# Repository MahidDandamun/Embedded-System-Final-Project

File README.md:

# Automated Pet Feeder System

An open-source, IoT-enabled automated pet feeder built with ESP32. Schedule feedings, monitor your pet's eating habits in real-time, and control everything from your phone.

<!--  -->

## Features

- **Scheduled Auto-Feeding** — 4 configurable daily feeding times
- **Manual Feed** — Physical button or remote trigger from mobile app
- **Food Level Monitoring** — Ultrasonic sensor detects container level (FULL / HALF / EMPTY)
- **Bowl Weight Tracking** — HX711 load cell measures food in the bowl
- **Pet Detection** — PIR motion sensor detects animal presence
- **Mobile App Control** — React Native app connects via Bluetooth (BLE)
- **Cloud Telemetry** — Azure IoT Hub (MQTT) + REST API for data logging
- **Web Flasher** — Flash firmware from your browser via USB — no IDE needed
- **Status Display** — 16x2 LCD + RGB LED + buzzer feedback
- **Safety Limits** — Daily max (200g), minimum interval (5 min), bowl-full detection

## Repository Structure

```
├── firmware/               # ESP32 firmware (PlatformIO / C++)
│   ├── include/            #   Header files + config
│   ├── src/                #   Source files
│   ├── test/               #   Calibration test
│   └── platformio.ini
├── PCB/                    # KiCad PCB design for breakout board
├── 3D-MODEL/               # Fusion 360 housing + component mounts
├── docs/                   # Specs for mobile app & web flasher
│   ├── MOBILE_APP_SPEC.md  #   React Native mobile app spec
│   └── WEB_FLASHER_SPEC.md #   Next.js web flasher spec
├── .agents/                # AI agent rules, workflows, context
└── README.md               # You are here
```

### Companion Repositories (Separate)

| Repo | Tech Stack | Purpose |
|------|-----------|---------|
| `petfeeder-mobile` | React Native (Expo) + TypeScript | Mobile app — BLE control, dashboard, history |
| `petfeeder-web` | Next.js + Web Serial API | Browser-based firmware flasher & calibration |

## Hardware Requirements

| Component | Model | Qty |
|-----------|-------|-----|
| Microcontroller | ESP32 DevKit C | 1 |
| Ultrasonic Sensor | HC-SR04 | 1 |
| Load Cell + Amplifier | 5kg load cell + HX711 | 1 |
| PIR Motion Sensor | Generic | 1 |
| Servo Motor | SG90 or MG90S | 1 |
| LCD Display | 16x2 I2C (address 0x27) | 1 |
| RTC Module | DS1302 | 1 |
| RGB LED | Common cathode | 1 |
| Active Buzzer | 5V | 1 |
| Push Buttons | IP65 12mm momentary (x2) | 2 |
| Power Supply | 5V 2A, 5.5x2.1mm barrel jack | 1 |
| Rocker Switch | SPST | 1 |
| Custom PCB | See `PCB/` directory | 1 |
| 3D-Printed Housing | See `3D-MODEL/` directory | 1 |

## Quick Start

### 1. Clone

```bash
git clone https://github.com/MahidDandamun/Embedded-System-Final-Project.git
cd Embedded-System-Final-Project
```

### 2. Configure Secrets

```bash
cd firmware
cp include/secrets.h.template include/secrets.h
```

Edit `firmware/include/secrets.h` with your credentials:

```c
#define ENV_WIFI_SSID       "YourWiFi"
#define ENV_WIFI_PASSWORD   "YourPassword"
#define ENV_MQTT_SERVER     "your-hub.azure-devices.net"
#define ENV_MQTT_PORT       8883
#define ENV_DEVICE_ID       "petfeeder"
#define ENV_SAS_TOKEN       "SharedAccessSignature sr=..."
#define ENV_MQTT_USERNAME   "your-hub.azure-devices.net/petfeeder/?api-version=2021-04-12"
#define ENV_DATABASE_ENDPOINT "https://your-api.azurewebsites.net/api/devices/status"
```

> **Never commit `secrets.h`** — it's in `.gitignore`.

### 3. Build & Flash

```bash
# Install PlatformIO CLI
pip install platformio

# Build
pio run

# Upload to ESP32
pio run -t upload

# Monitor serial output
pio device monitor
```

### 4. Calibrate Load Cell

```bash
# Upload calibration firmware
pio test -e esp32dev -f test_calibration
```

Follow the serial prompts to find your `CALIBRATION_FACTOR`, then update it in `firmware/include/config.h`.

### 5. Assemble Hardware

1. Print the housing from `3D-MODEL/` (see [3D-MODEL/README.md](3D-MODEL/README.md))
2. Solder or order the PCB from `PCB/` (see [PCB/README.md](PCB/README.md))
3. Wire everything per the [pin mapping](firmware/README.md#pin-mapping-pcb-v2)
4. Power on and verify via serial monitor

## Architecture

```
┌─────────────┐     BLE      ┌─────────────┐
│  Mobile App │◄────────────►│    ESP32     │
│ (React Native)             │  Firmware    │
└─────────────┘              │             │
                             │  Sensors:    │
┌─────────────┐    MQTT      │  - Ultrasonic│
│  Azure IoT  │◄────────────►│  - Load Cell │
│    Hub      │              │  - PIR       │
└──────┬──────┘              │  - RTC       │
       │                     │             │
       │ REST                │  Actuators:  │
       ▼                     │  - Servo     │
┌─────────────┐              │  - LCD       │
│  Backend DB │              │  - RGB LED   │
│  (REST API) │              │  - Buzzer    │
└─────────────┘              └──────┬───────┘
                                    │ USB
┌─────────────┐    Web Serial      │
│  Web Flasher│◄───────────────────┘
│  (Next.js)  │
└─────────────┘
```

## Mobile App

The companion mobile app (separate repo) provides:

- **Dashboard** — Real-time sensor data, feeding status, pet detection
- **Feeding History** — Charts and timeline of all feeding events
- **Schedule Control** — Edit feeding times and portion sizes
- **BLE Connection** — Direct Bluetooth communication with the feeder
- **Push Notifications** — Low food alerts, missed feeding warnings

**Tech Stack:** React Native (Expo) + TypeScript + Zustand + react-native-ble-plx

See full spec: [docs/MOBILE_APP_SPEC.md](docs/MOBILE_APP_SPEC.md)

## Web Flasher

A browser-based tool to flash firmware and calibrate sensors — no IDE installation required:

1. Connect ESP32 via USB-C
2. Enter WiFi/cloud credentials in the web form
3. Click "Flash" — firmware uploads directly from Chrome
4. Run guided sensor calibration

**Tech Stack:** Next.js + TypeScript + Web Serial API + esptool-js

See full spec: [docs/WEB_FLASHER_SPEC.md](docs/WEB_FLASHER_SPEC.md)

## Pin Mapping

| Function | GPIO | Notes |
|----------|------|-------|
| Power Relay | 27 | System power control |
| Button 1 (Refill) | 15 | INPUT_PULLUP |
| Button 2 (Feed) | 0 | INPUT_PULLUP |
| Ultrasonic Trig | 32 | |
| Ultrasonic Echo | 33 | |
| PIR Sensor | 25 | |
| HX711 DOUT | 5 | |
| HX711 SCK | 23 | |
| RGB Red | 13 | |
| RGB Green | 12 | |
| RGB Blue | 14 | |
| Buzzer | 26 | Active buzzer |
| Servo | 4 | SG90/MG90S |
| RTC IO | 16 | DS1302 |
| RTC SCLK | 17 | DS1302 |
| RTC CE | 2 | DS1302 |

## Security Notes

- All credentials are stored in `secrets.h` which is **never committed** to git
- A `secrets.h.template` is provided as reference
- Azure SAS tokens should be rotated regularly
- For production: replace `setInsecure()` with proper TLS certificate pinning
- If you ever accidentally commit secrets: **rotate ALL credentials immediately**

### Regarding Credentials in Git History

The credentials found in older commits have been **revoked and are no longer valid**. The WiFi password, Azure SAS tokens, and API endpoints from the git history are all invalidated. Always generate your own fresh credentials.

## Contributing

1. Fork the repository
2. Create a feature branch (`git checkout -b feat/amazing-feature`)
3. Use conventional commits (`feat:`, `fix:`, `docs:`, `refactor:`)
4. Ensure no secrets are in your commits
5. Open a Pull Request

## License

This project is licensed under the [MIT License](LICENSE).

## Authors

- Irish Micole Cando
- Jelisha Bugnon
- Angela Corpuz
- Mahid Dandamun
- Miguel Alfonso Neri

---

> Built as a final project for Embedded Systems course. Designed to be open-source, educational, and production-ready.

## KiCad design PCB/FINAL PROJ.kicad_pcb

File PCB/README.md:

# PCB — Pet Feeder Breakout Board

KiCad PCB design for the ESP32 pet feeder breakout/carrier board.

## Files

| File | Description |
|------|-------------|
| `FINAL PROJ.kicad_sch` | Schematic |
| `FINAL PROJ.kicad_pcb` | PCB layout |
| `FINAL PROJ.kicad_pro` | KiCad project |
| `FINAL PROJ.step` | 3D model of PCB |
| `freerouting.dsn` | Auto-routing export |
| `config.h` | Pin mapping reference (mirrors firmware config) |

## Features

- ESP32 DevKit C socket
- Breakout headers for all sensors (HC-SR04, PIR, HX711, DS1302)
- Servo connector (5V + signal)
- I2C header for LCD
- RGB LED + buzzer outputs
- 5V barrel jack power input with rocker switch
- Dual push-button inputs

## Opening the Design

1. Install [KiCad](https://www.kicad.org/) (v7+ recommended)
2. Open `FINAL PROJ.kicad_pro`
3. Schematic → `FINAL PROJ.kicad_sch`
4. PCB Layout → `FINAL PROJ.kicad_pcb`

## Manufacturing

Export Gerbers from KiCad and upload to your preferred PCB fab (JLCPCB, PCBWay, OSH Park, etc.).

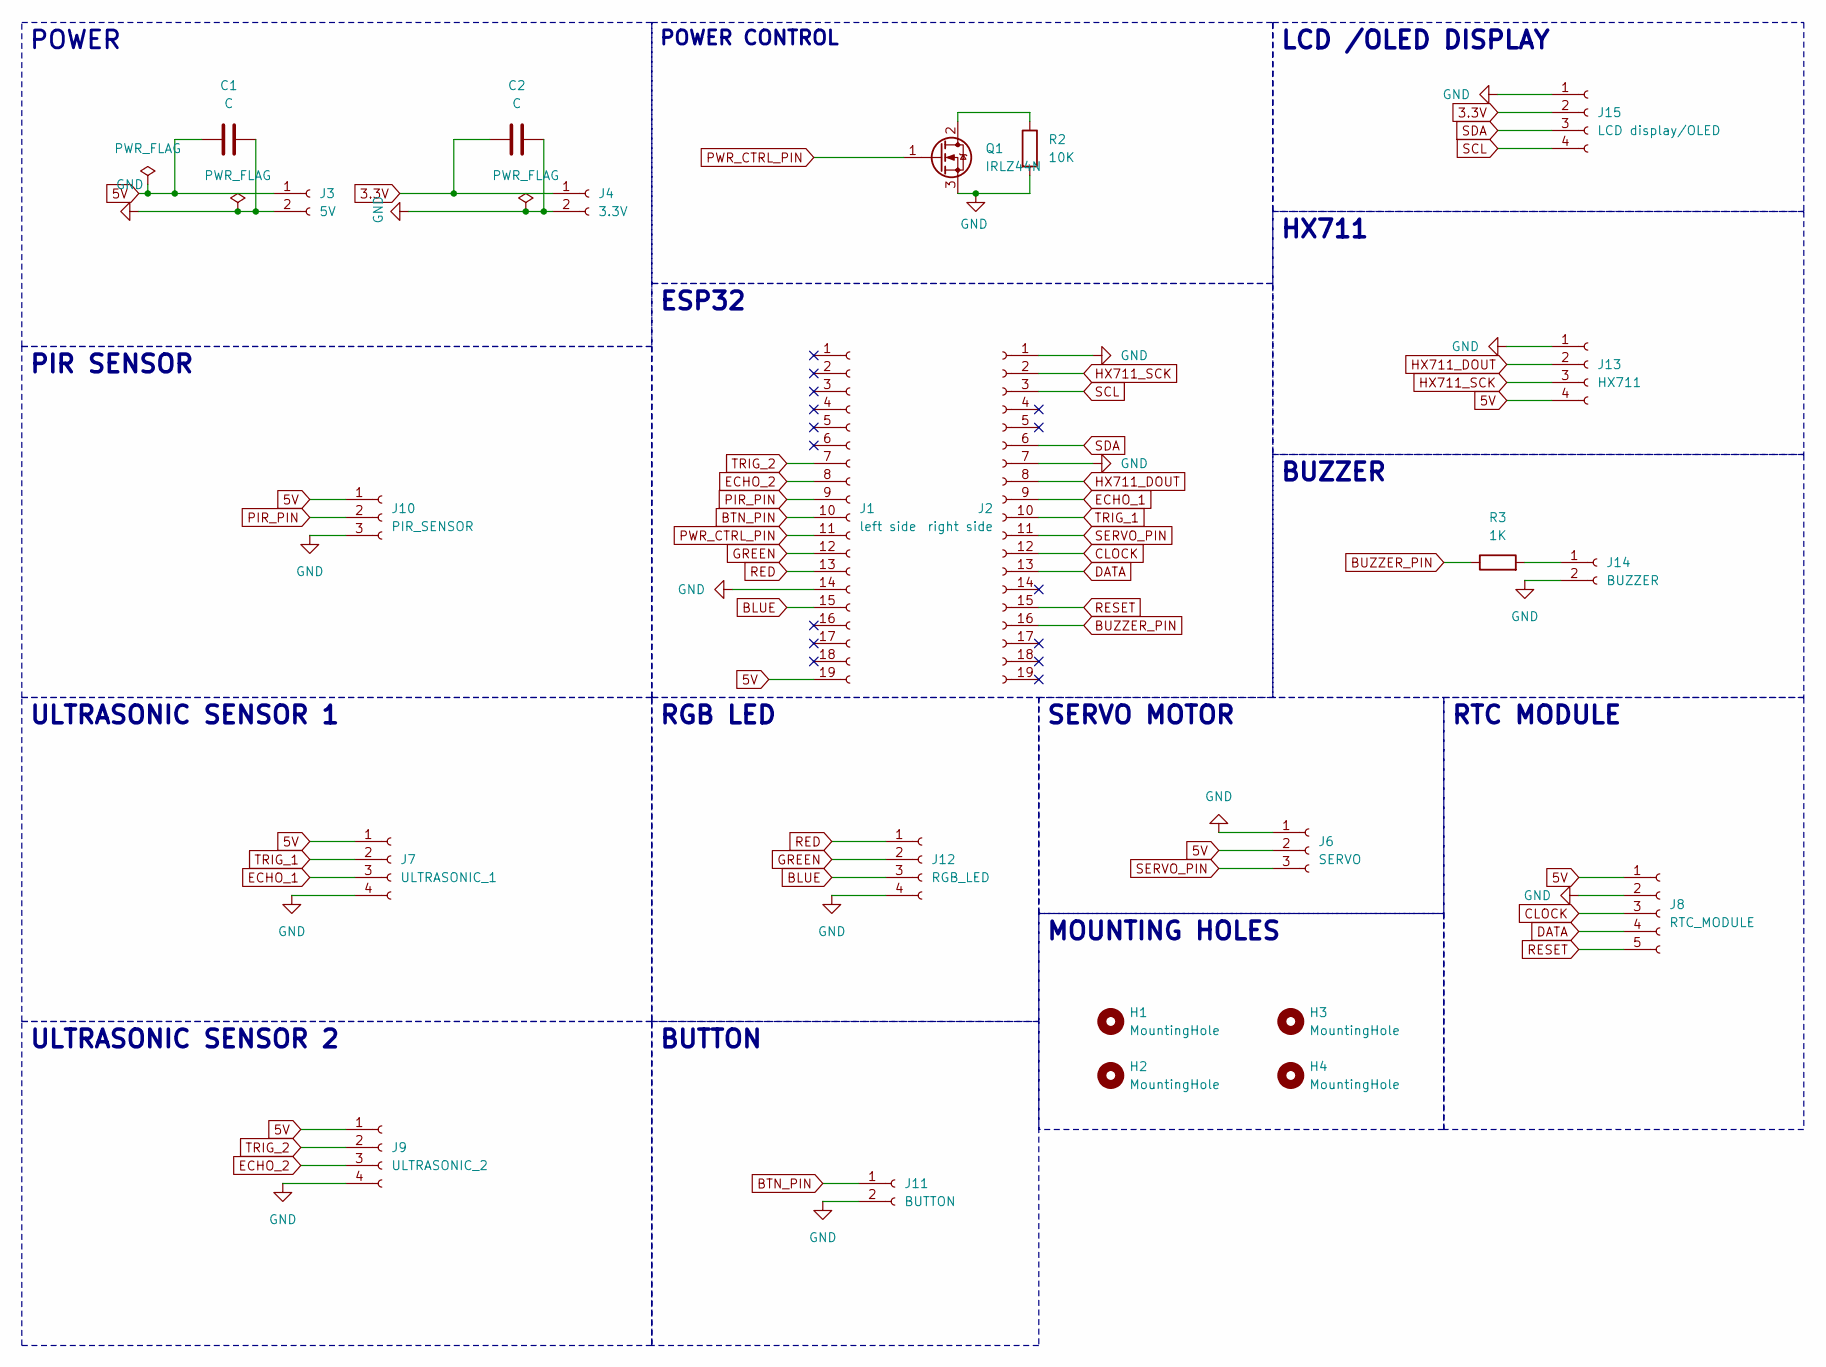
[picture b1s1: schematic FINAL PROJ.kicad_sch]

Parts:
C1, C2: C; C_Disc_D4.3mm_W1.9mm_P5.00mm
H1, H2, H3, H4: MountingHole; MountingHole_3.2mm_M3
J1: left side; PinSocket_1x19_P2.54mm_Vertical
J2: right side; PinSocket_1x19_P2.54mm_Vertical
J3: 5V; JST_EH_B2B-EH-A_1x02_P2.50mm_Vertical
J4: 3.3V; JST_EH_B2B-EH-A_1x02_P2.50mm_Vertical
J6: SERVO; JST_EH_B3B-EH-A_1x03_P2.50mm_Vertical
J7: ULTRASONIC_1; JST_EH_B4B-EH-A_1x04_P2.50mm_Vertical
J8: RTC_MODULE; PinSocket_1x05_P2.54mm_Vertical
J9: ULTRASONIC_2; JST_EH_B4B-EH-A_1x04_P2.50mm_Vertical
J10: PIR_SENSOR; JST_EH_B3B-EH-A_1x03_P2.50mm_Vertical
J11: BUTTON; JST_EH_B2B-EH-A_1x02_P2.50mm_Vertical
J12: RGB_LED; JST_EH_B4B-EH-A_1x04_P2.50mm_Vertical
J13: HX711; PinSocket_1x04_P2.54mm_Vertical
J14: BUZZER; JST_EH_B2B-EH-A_1x02_P2.50mm_Vertical
J15: LCD display/OLED; JST_EH_B4B-EH-A_1x04_P2.50mm_Vertical
Q1: IRLZ44N; TO-220-3_Vertical
R2: 10K; R_Axial_DIN0309_L9.0mm_D3.2mm_P12.70mm_Horizontal
R3: 1K; R_Axial_DIN0309_L9.0mm_D3.2mm_P12.70mm_Horizontal

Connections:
3.3V: C2.1, J4.1, J15.2
5V: C1.1, J1.19, J3.1, J6.2, J7.1, J8.1, J9.1, J10.1, J13.4
BLUE: J1.15, J12.3
BTN_PIN: J1.10, J11.1
BUZZER_PIN: J2.16, R3.1
CLOCK: J2.12, J8.3
DATA: J2.13, J8.4
ECHO_1: J2.9, J7.3
ECHO_2: J1.8, J9.3
GREEN: J1.12, J12.2
HX711_DOUT: J2.8, J13.2
HX711_SCK: J2.2, J13.3
unnamed: J14.1, R3.2
unnamed: Q1.2 (D), R2.1
PIR_PIN: J1.9, J10.2
PWR_CTRL_PIN: J1.11, Q1.1 (G)
RED: J1.13, J12.1
RESET: J2.15, J8.5
SCL: J2.3, J15.4
SDA: J2.6, J15.3
SERVO_PIN: J2.11, J6.3
TRIG_1: J2.10, J7.2
TRIG_2: J1.7, J9.2

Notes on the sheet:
HX711
PIR SENSOR
RGB LED
BUTTON
MOUNTING HOLES
ESP32
ULTRASONIC SENSOR 1
ULTRASONIC SENSOR 2
BUZZER
POWER CONTROL
RTC MODULE
POWER
LCD /OLED DISPLAY
SERVO MOTOR

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
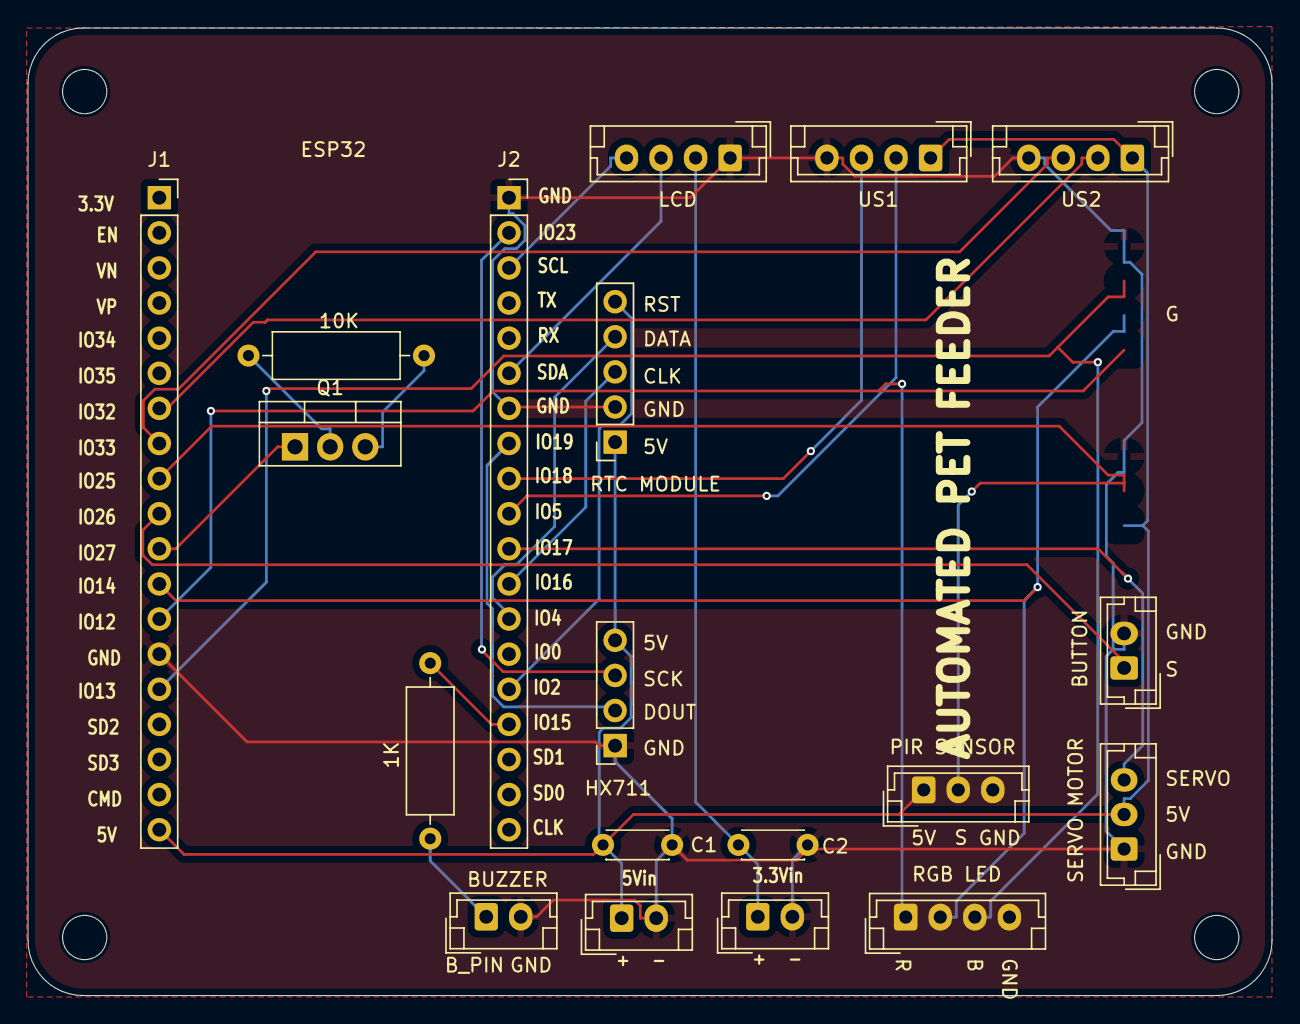
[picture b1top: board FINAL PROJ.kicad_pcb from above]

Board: 2 copper layers, 90.0 x 70.0 mm, 23 parts (1 on the bottom side), 25 nets.

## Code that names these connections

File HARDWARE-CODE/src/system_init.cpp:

#include "system_init.h"

void systemStart()
{
  initializeLCD();
  initializeRTC();
  initializePins();
  initializeWiFi();
  initializeSensors();
  feederSystem.initialized = true;

  lcd.clear();
  lcd.setCursor(0, 0);
  lcd.print("Pet Feeder Ready");
  lcd.setCursor(0, 1);
  lcd.print("HTTP Mode");
}

void initializeLCD()
{
  lcd.init();
  lcd.backlight();
  lcd.setCursor(0, 0);
  lcd.print("Initializing...");
}

void initializeRTC()
{
  if (rtc.begin())
  {
    feederSystem.rtcReady = true;
    if (rtc.lostPower())
      rtc.adjust(DateTime(F(__DATE__), F(__TIME__)));

    DateTime now = rtc.now();
    timeData.lastAutoFeedTime = now;
    timeData.nextScheduledFeed = getNextScheduledFeedTime(now);
    timeData.currentTimeString = formatTime(now);
    timeData.nextFeedTimeString = formatTime(timeData.nextScheduledFeed);

    lcd.setCursor(0, 1);
    lcd.print("RTC: OK");
  }
  else
  {
    feederSystem.rtcReady = false;
    feederSystem.autoFeedingEnabled = false;
    lcd.setCursor(0, 1);
    lcd.print("RTC: FAILED");
  }
  delay(1000);
}

void initializePins()
{
  pinMode(POWER_PIN, OUTPUT);
  digitalWrite(POWER_PIN, HIGH);
  feederSystem.powerOn = true;

  pinMode(BUTTON1_PIN, INPUT_PULLUP);
  pinMode(BUTTON2_PIN, INPUT_PULLUP);
  pinMode(ULTRASONIC_TRIG_PIN, OUTPUT);
  pinMode(ULTRASONIC_ECHO_PIN, INPUT);
  pinMode(PIR_PIN, INPUT);
  pinMode(HX711_DOUT_PIN, INPUT);
  pinMode(HX711_SCK_PIN, OUTPUT);
  pinMode(RED_PIN, OUTPUT);
  pinMode(GREEN_PIN, OUTPUT);
  pinMode(BLUE_PIN, OUTPUT);
  pinMode(BUZZER_PIN, OUTPUT);

  myServo.attach(SERVO_PIN);
  myServo.write(0);
}

void initializeWiFi()
{
  lcd.clear();
  lcd.setCursor(0, 0);
  lcd.print("Connecting WiFi");
  WiFi.begin(WIFI_SSID, WIFI_PASSWORD);

  int attempts = 0;
  while (WiFi.status() != WL_CONNECTED && attempts < WIFI_RETRY_ATTEMPTS)
  {
    delay(500);
    lcd.setCursor(attempts % LCD_COLUMNS, 1);
    lcd.print(".");
    attempts++;
  }

  lcd.clear();
  lcd.setCursor(0, 0);
  if (WiFi.status() == WL_CONNECTED)
  {
    lcd.print("WiFi Connected");
    lcd.setCursor(0, 1);
    lcd.print(WiFi.localIP());
    delay(3000);
  }
  else
  {
    lcd.print("WiFi Failed");
    lcd.setCursor(0, 1);
    lcd.print("Check Settings");
  }
}

void initializeSensors()
{
  // Initialize scale and other sensors
  scale.begin(HX711_DOUT_PIN, HX711_SCK_PIN);
  // Add any additional sensor initialization here
}

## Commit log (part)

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2025-06-11 feat(3d model): Components for 3d model were added
2025-06-11 feat(hardware-code): Code for the hardware were added
2025-06-11 feat(pcb): Pcb design for breakout board was added
2025-06-11 Added System Power consumption and its diagram
2025-06-11 Updated README file
2025-06-14 refactor(hardware-code): database sending and fixed errors
2025-06-14 sending of data to database
2025-06-15 refactor: pin config
2025-06-15 feat: add load cell sensor reading
2025-06-15 feat: food dispensing check
2025-06-15 feat: Implement servo motor control on website
2025-06-16 refactor: updated pcb
2025-06-17 2 43 update
2025-06-20 refactor: Fixed secrets
2025-06-20 Initial commit - clean version without secrets
2025-06-20 Add security documentation and secrets template
2025-06-20 init
2026-03-10 Add core functionality for pet feeder system
    - Implement main application logic in main.cpp, including setup and loop functions.
    - Create network_manager.cpp for handling MQTT setup, connection, and backend communication.
    - Develop sensor_manager.cpp to manage sensor readings and status updates.
    - Initialize system components in system_init.cpp, including WiFi and RTC setup.
    - Implement time management functions in time_manager.cpp for scheduling feeds and formatting timestamps.
    - Add load cell calibration test in test_calibration.cpp for determining calibration factor.
